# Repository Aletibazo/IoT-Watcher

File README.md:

# IoT-Watcher

Open source monitoring system for IT infrastructures using IoT sensors.

Related paper: https://doi.org/10.1007/978-3-031-48590-9_15

## Motivation

In Data Centers there are usually monitoring solutions offered by the manufacturer, which integrate all the equipment and sensors that make up the solution in a single system. In the CITIC data centre, all the sensors are integrated into an APC system that allows the thresholds of each type of sensor to be managed and alerts to be configured.

These proprietary solutions work very well, but it is difficult to add external elements to these systems, since they have closed APIs and it is difficult to obtain the appropriate documentation. In the specific case of the CITIC, it is desired to be able to integrate the monitoring of the servers housed in the CPD cabinets together with the monitoring of the environmental parameters of the room, thus centralising all the elements that make up the CPD and that are managed by the administrator.

## Description

This project aims to develop an open, multi-platform system that allows for the addition of different types of sensors and machines. With this secondary objective in mind, developments will be made on open hardware platforms for the sensor part and, whenever possible, open-source operating systems, libraries, external programs, etc. will be used with the goal of having a system that is as open and compatible as possible.

The monitoring server will be based on Zabbix, a widely used monitoring tool in the systems world. In the first phase, servers will be added to this system using the Zabbix agents for Windows, Linux and VMware, and their correct operation will be checked by taking data and comparing it with the servers themselves. The monitoring server forms the basis of the project, and once it is deployed and tested, the sensor section will be developed.

Sensors compatible with open-source and open-hardware Arduino boards will be used, always keeping in mind that the sensors used in this project can be replaced by others with similar characteristics. In the particular case of this project, temperature, humidity, presence and electrical consumption sensors will be used. First, the Arduino program will be developed to read data from the sensors and send it to a Raspberry Pi that will be responsible for centralizing the data from all the Arduinos in the infrastructure and sending it to the Zabbix server. Then each sensor will be placed in its corresponding place in the DC, for which issues such as autonomy, placement in racks, etc. will be taken into account.

An open-source application with the MQTT protocol will be used for data transmission between the Arduinos and the Raspberry Pi. With the rise of the IoT, multiple open-source projects have emerged to control home automation elements, so one of these projects will be used to collect all the data from the sensors and the necessary functionalities will be added to send the data to the configured Zabbix server. To achieve this communication between Raspberry and Zabbix, a specific agent will be developed.

The possibility of implementing a prediction system based on Machine Learning models that launches alerts of possible failures in the infrastructure will be considered. The system is intended to be able to alert of failures that may occur in all elements of the DC - from end-of-life warnings for disks to possible failures in the cooling system - based on historical data and real-time data.

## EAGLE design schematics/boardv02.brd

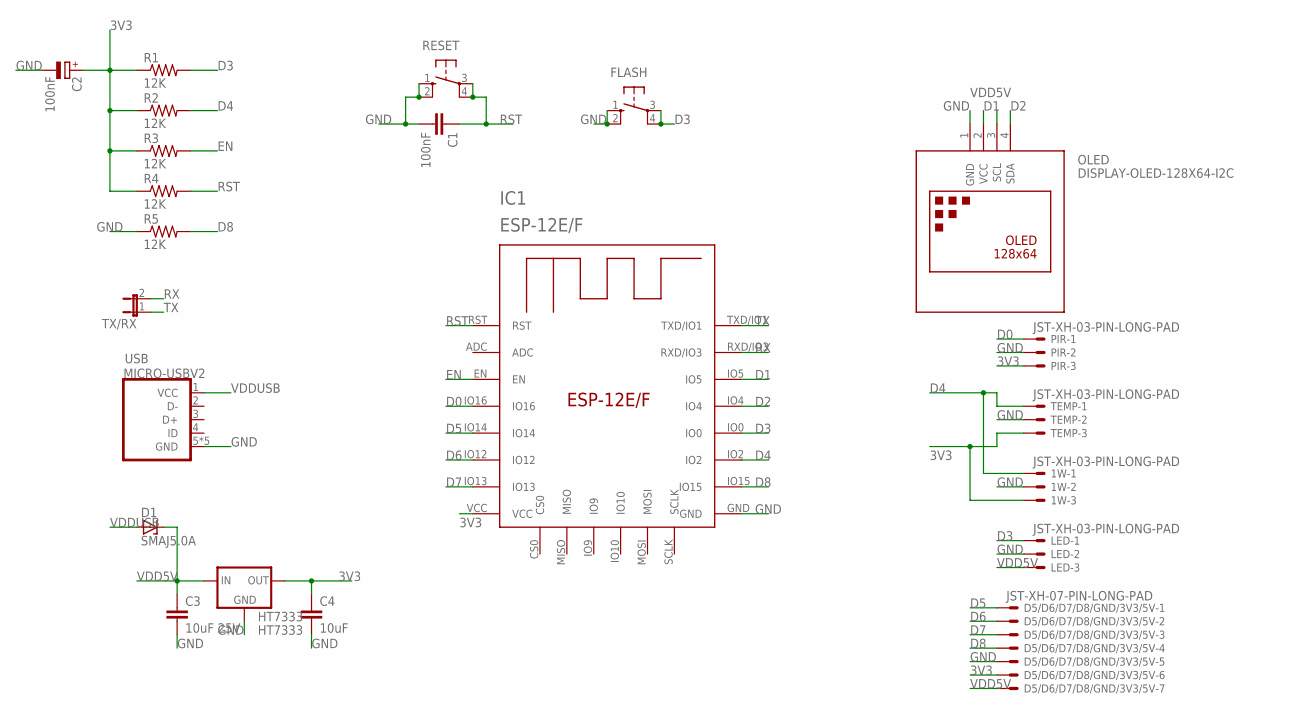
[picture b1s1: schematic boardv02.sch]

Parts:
1W: JST-XH-03-PIN-LONG-PAD; JST-XH-03-PACKAGE-LONG-PAD
C1: 100nF; C0805
C2: 100nF; R/2012-12R
C3: 10uF 25V; C0805
C4: 10uF; C0805
D1: SMAJ5.0A; DO214AC
D5/D6/D7/D8/GND/3V3/5V: JST-XH-07-PIN-LONG-PAD; JST-XH-07-PACKAGE-LONG-PAD
FLASH: 10-XX; B3F-10XX
HT7333: HT7333; SOT-89
IC1: ESP-12E/F; ESP-12E
LED: JST-XH-03-PIN-LONG-PAD; JST-XH-03-PACKAGE-LONG-PAD
OLED: DISPLAY-OLED-128X64-I2C
PIR: JST-XH-03-PIN-LONG-PAD; JST-XH-03-PACKAGE-LONG-PAD
R1, R2, R3, R4, R5: 12K; R1206
RESET: 10-XX; B3F-10XX
TEMP: JST-XH-03-PIN-LONG-PAD; JST-XH-03-PACKAGE-LONG-PAD
TX/RX: JP1E; JP1
USB: MICRO-USBV2; MICRO-USB-2

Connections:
3V3: 1W.3, C2.+, C4.1, D5/D6/D7/D8/GND/3V3/5V.6, HT7333.1 (OUT), IC1.VCC, PIR.3, R1.1, R2.1, R3.1, R4.1, TEMP.3
D0: IC1.IO16, PIR.1
D1: IC1.IO5, OLED.3 (SCL)
D2: IC1.IO4, OLED.4 (SDA)
D3: FLASH.3, FLASH.4 (P1), IC1.IO0, LED.1, R1.2
D4: 1W.1, IC1.IO2, R2.2, TEMP.1
D5: D5/D6/D7/D8/GND/3V3/5V.1, IC1.IO14
D6: D5/D6/D7/D8/GND/3V3/5V.2, IC1.IO12
D7: D5/D6/D7/D8/GND/3V3/5V.3, IC1.IO13
D8: D5/D6/D7/D8/GND/3V3/5V.4, IC1.IO15, R5.2
EN: IC1.EN, R3.2
GND: 1W.2, C1.2, C2.-, C3.2, C4.2, D5/D6/D7/D8/GND/3V3/5V.5, FLASH.1 (S), FLASH.2 (S1), HT7333.2 (GND), IC1.GND, LED.2, OLED.1 (GND), PIR.2, R5.1, RESET.1 (S), RESET.2 (S1), TEMP.2, USB.5 (GND), USB.P$1 (GND), USB.P$2 (GND), USB.P$3 (GND), USB.P$4 (GND)
RST: C1.1, IC1.RST, R4.2, RESET.3, RESET.4 (P1)
RX: IC1.RXD/IO3, TX/RX.2
TX: IC1.TXD/IO1, TX/RX.1
VDD5V: C3.1, D1.C, D5/D6/D7/D8/GND/3V3/5V.7, HT7333.3 (IN), HT7333.4 (IN), LED.3, OLED.2 (VCC)
VDDUSB: D1.A, USB.1 (VCC)

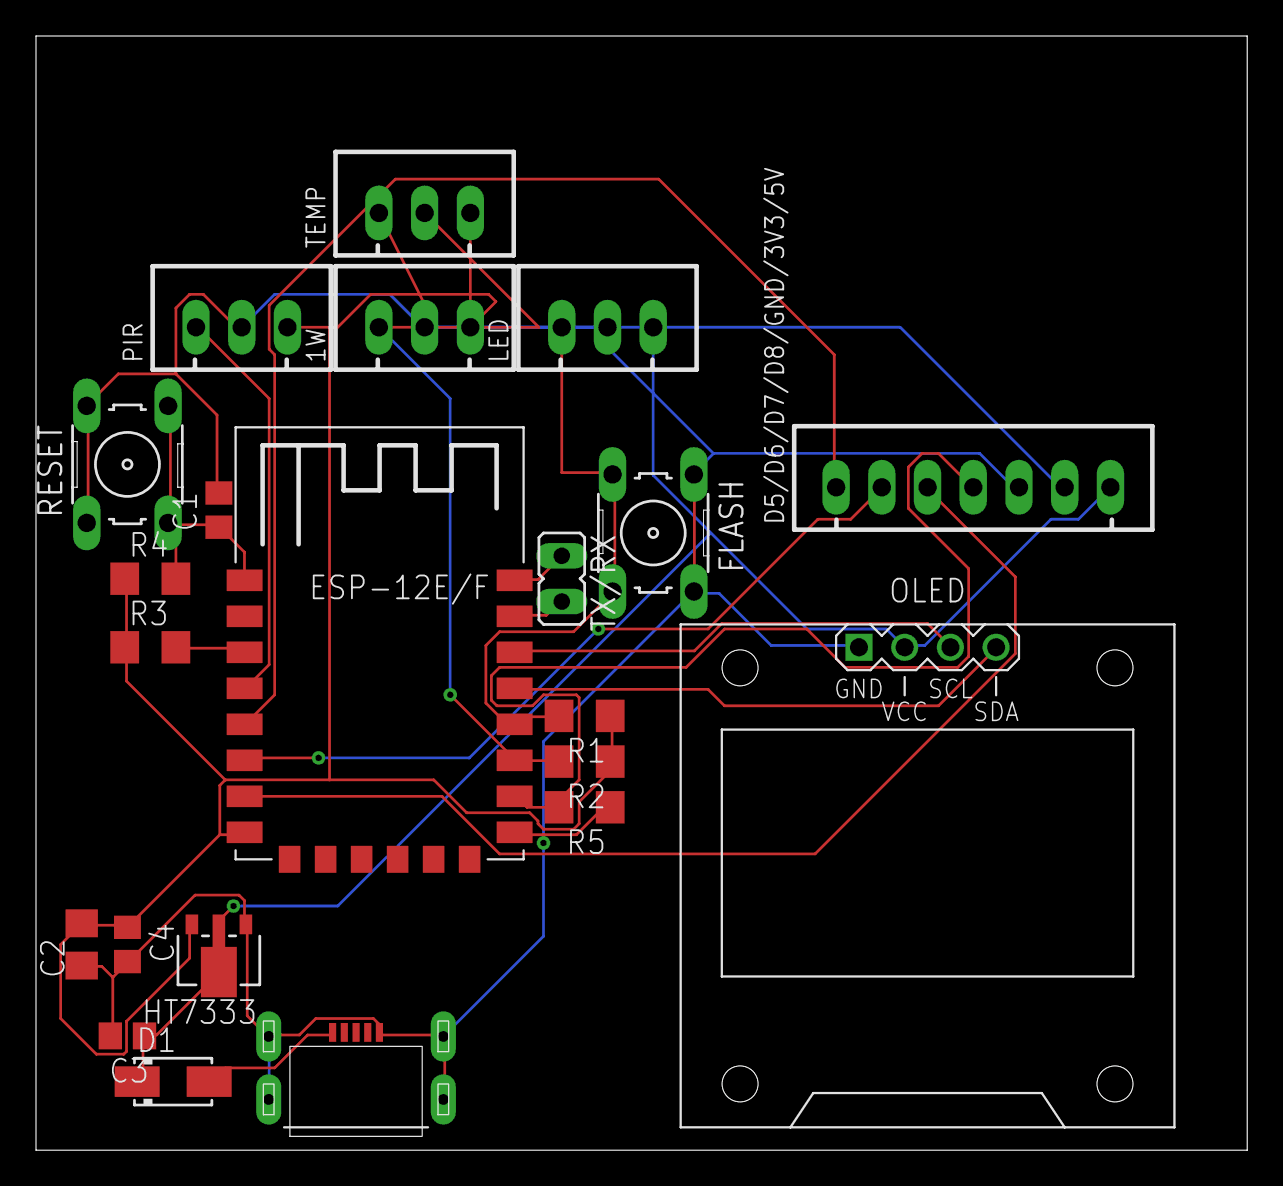
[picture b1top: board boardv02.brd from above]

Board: 2 copper layers, 67.3 x 61.9 mm, 22 parts (0 on the bottom side), 17 nets.

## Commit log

2020-09-28 Initial load from GitHub code
2021-05-21 Create sensor_board.ino
    Added sensor_board.ino, intended to be the official firmware version for the sensor board designed for this project, integrating DS18B20, PIR and LED
2021-11-22 Update sensor_board.ino
    Several changes here.
    Implemented MQTT messaging system, so HomeAssistant can auto discover. Note that topic prefix for discovery has to be set on HomeAssistant configuration.yaml so it matches the one we use here.
    Added PIR sensor.
    Added humidity sensor using DHT library. Set on D5.
    Changes on display settings, using print instead of drawStr now.
2022-01-24 Replaced DHT.h library with DHTesp.h, now DHT11 sensor is working on D5
2023-09-25 Added SensorBoard Eagle Project, witch schematics for the custom board. Edited gitignore file so it doesn't upload unnecesary files from Eagle.

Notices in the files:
parts and their libraries:
diy-modules: Released under the Creative Commons Attribution 4.0 International License: http://creativecommons.org/licenses/by/4.0
